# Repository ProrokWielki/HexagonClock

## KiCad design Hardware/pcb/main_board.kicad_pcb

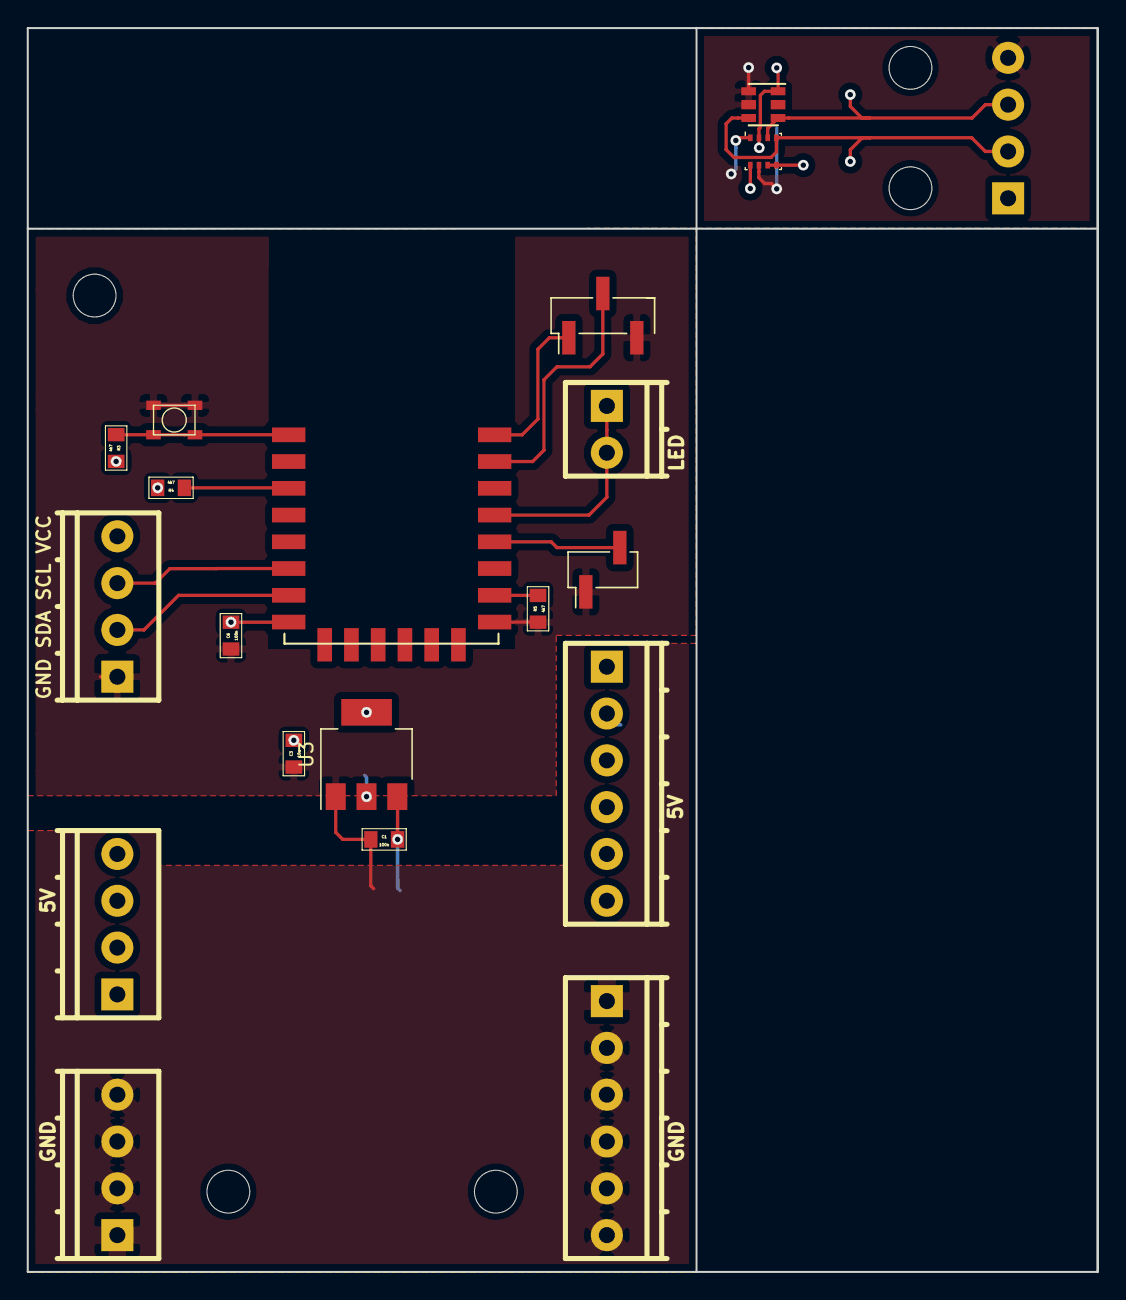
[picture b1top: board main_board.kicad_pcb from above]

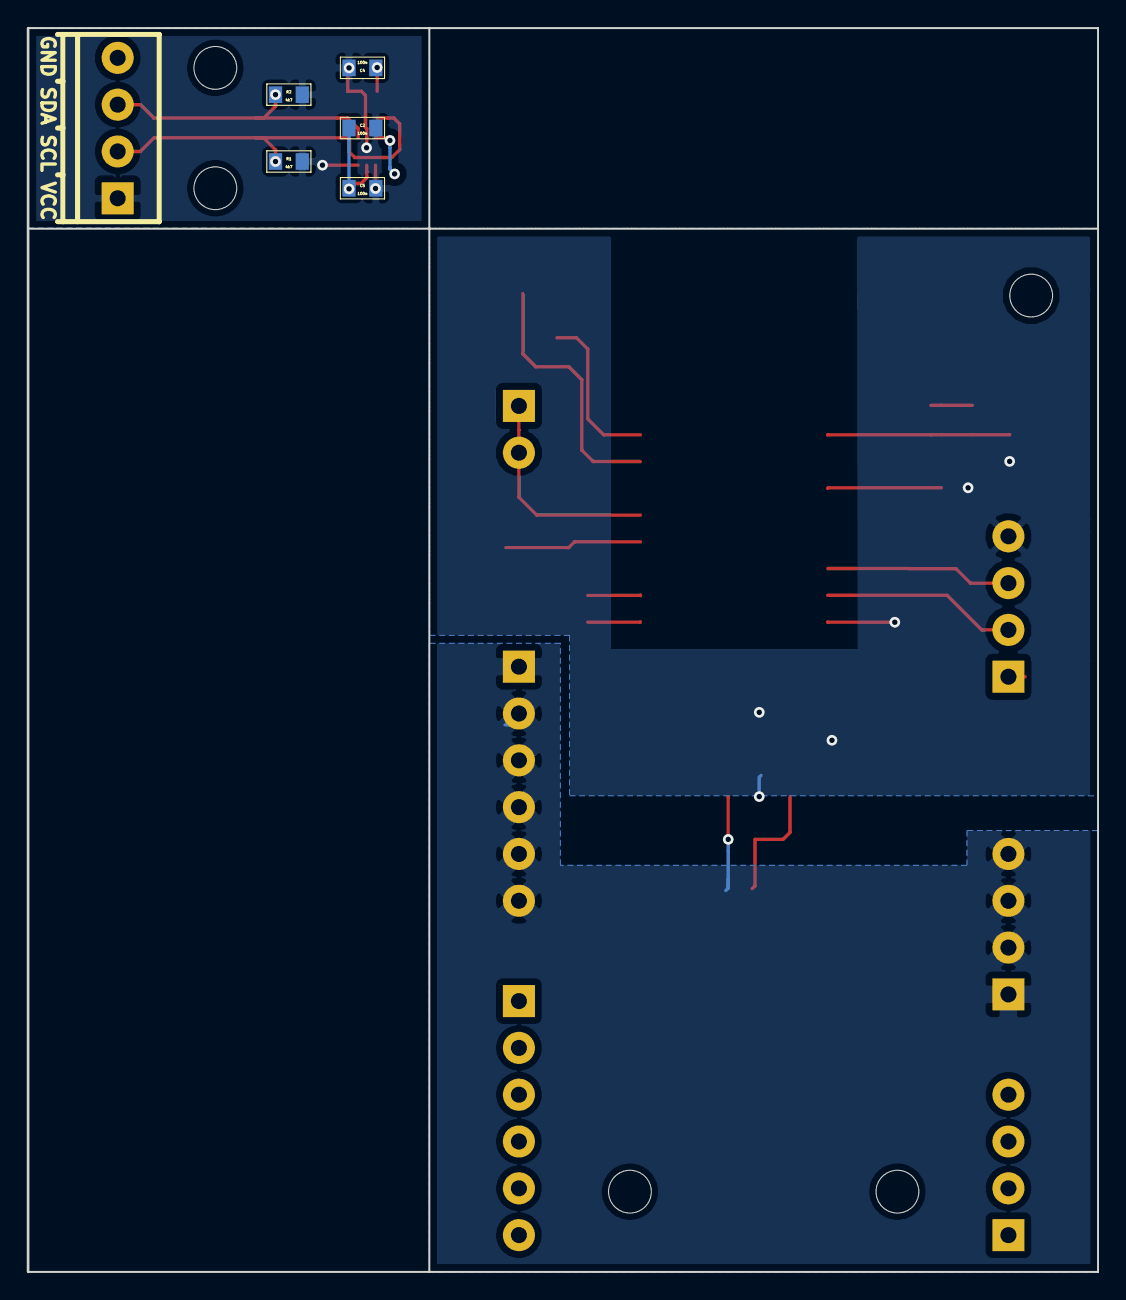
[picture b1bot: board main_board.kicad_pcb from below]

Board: 2 copper layers, 80.0 x 93.0 mm, 25 parts (6 on the bottom side), 12 nets.

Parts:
C1, C2, C4, C5, C6: 100n; 0805
C3: 10u; 0805
J1: 5V; pt_1,5-4-3,5-h
J2: GND; pt_1,5-4-3,5-h
J3: 5V; pt_1,5-6-3,5-h
J4: GND; pt_1,5-6-3,5-h
J5, J6: GND SDA SCL VCC; pt_1,5-4-3,5-h
J7: LED; pt_1,5-2-3,5-h
J8: Tx Rx GND; Pin_Header_Straight_1x03_Pitch2.54mm_SMD_Pin1Left
JP1: Program; Pin_Header_Straight_1x02_Pitch2.54mm_SMD_Pin1Left
R1, R2, R3, R4, R5: 4k7; 0805
SW1: Reset; 3.3x3.3 push button
U1: BME280; Bosch_LGA-8_2.5x2.5mm_P0.65mm_ClockwisePinNumbering
U2: APDS-9301; Broadcom_APDS-9301
U3: LD1117-3.3; SOT-223-3_TabPin2
U4: ESP-12E; ESP-12E_SMD

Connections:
+3V3: C2.1, C3.1, C4.1, C5.1, C6.1, J5.1, J6.4, R1.1, R2.1, R3.1, R4.1, U1.2, U1.5, U1.6, U1.8, U2.1, U3.2, U4.8
+5V: C1.1, J1.1, J1.2, J1.3, J1.4, J3.1, J3.2, J3.3, J3.4, J3.5, J3.6, U3.3
/SCL: J5.2, J6.3, R1.2, U1.4, U2.4, U4.6
/SDA: J5.3, J6.2, R2.2, U1.3, U2.5, U4.7
GNDD: C1.2, C2.2, C3.2, C4.2, C5.2, C6.2, J2.1, J2.2, J2.3, J2.4, J4.1, J4.2, J4.3, J4.4, J4.5, J4.6, J5.4, J6.1, J8.3, JP1.1, R5.2, SW1.1, SW1.3, U1.1, U1.7, U2.2, U2.3, U3.1, U4.9
unnamed: J7.1, J7.2, U4.13
unnamed: J8.1, U4.16
unnamed: J8.2, U4.15
unnamed: JP1.2, U4.12
unnamed: R3.2, SW1.2, SW1.4, U4.1
unnamed: R4.2, U4.3
unnamed: R5.1, U4.10

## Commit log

2020-02-11 Added display and font concept pictures
2020-02-11 added 3d design (fusion 360) and stl files of the pixel
2020-02-11 adde 3d design (fusion 360) and stl files of the control box
2020-02-11 Schematic, pcb and gerber files of the main board
2020-02-16 clanfg-format file added
2020-02-16 wifi config file add
2020-02-16 Added gitignore file
2020-02-16 mqtt config file added
2020-02-16 mqtt_config.h added to git ignore
2020-02-16 Added config for the apds9301
2020-02-16 added i2c config
2020-02-16 added leds config
2020-02-16 added helpers for ota, mqtt and display handling
2020-02-16 added main file
2020-02-16 fixed typo, changed subscribe helper function signature - so there is one place where subscribed topics are listed
2020-03-15 added fill_led
2020-03-15 Added Views
2020-03-15 Added Font
2020-03-15 Added main script
2020-07-25 spread out geting data from the clock
2021-01-30 fixed minor bugs/typos and added watchdog
2021-04-18 added debug prints, and added reset after 10 unsucesfull connections
